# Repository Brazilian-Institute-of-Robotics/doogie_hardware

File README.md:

# Doogie Hardware
This repository is intend to gather all the files regarding the Doogie Mouse robot hardware and briefly explain about robot's electronic architecture.

## Folder organization
- [Eagle]\: [Autocad Eagle] files (*.sch and *.brd) of top and bottom boards and a file used to check design rules (.dru)
- [Gerbers]\: Files used to manufacture the top and bottom boards
- [Libraries]\: Eagle libraries used in the layout of the Doogie Mouse robot boards
- [Schematics]\: Electronic schematics of top and bottom board in PDF format
- [BOM]\: Bill Of Materials

## Electronic architecture
The electronic architecture in the figure below demonstrates how Doogie Mousee components are electrically interconnected. For the purpose of better visualization, the voltage reference (Ground - GND) was omitted.

<p align="center">
<b>Figure 1: </b>Electronic architecture 
<br>
<br>

</p>

The Doogie is equipped with a Li-Ion battery with 3.6 V of nominal voltage. To make the battery voltage level compatible with the other components, two DC-DC converters are used. The first will supply 6 V exclusively for motors and emitting LEDs. The second is responsible for supplying the Raspberry Pi with 5 V. However, the components that are connected to the Raspberry Pi are powered by 3.3 V through an internal DC-DC converter on the microprocessor system board.

In order to facilitate the replication of the robot by users who want to use it, it was decided to use breakout boards, which are pre-assembled electronic boards. Doogie has six of them: two DC-DC voltage converters, an A/D converter, an IMU, an analog multiplexer and an H-Bridge. The other components, such as resistors, transistors, infrared LEDs, phototransistors and connectors, are soldered directly on the PCB.

Doogie components communicate and are controlled in several ways. The A/D converter and the IMU communicate with the Raspberry Pi via an I2C bus. As the specified A/D converter has only 4 channels (one for each infrared sensor), it was decided to use an analog multiplexer to allow the battery voltage value to be obtained as well. This multiplexer is controlled by digital pins from the processing unit. Finally, the control of the motors is performed by an H bridge with two independent channels. This power driver allows the directions of rotation of the motors to be controlled by digital pins from the Raspberry Pi while the speed control is performed by PWM.

For detailed description of components connections, see the electronic schematics [doogie_bottom_board](Schematics/doogie_bottom_board.pdf) and [doogie_top_board](Schematics/doogie_top_board.pdf).

## Boards overview
<p align="center">
<b>Top Board</b>
<br>
<br>

</p>

<p align="center">
<b>Bottom Board</b>
<br>
<br>

</p>

## Assembly Instructions
See [Hardware Setup] on Doogie wiki page!

## Purpose of the Project

Doogie Mouse platform was originally developed in 2019 as an undergraduate thesis (Theoprax methodoly) at Centro Universitário SENAI CIMATEC in partnership with Brazillian Institute of Robotics, for teaching principles of artificial intelligence using high level framework for writing and reusing robot software.

It's a open source project and expects modifications and contributions from it's users. 

## Change Log
#### [1.0] - 2019-12-10
- First version

## Bugs & Feature Requests
Please report bugs and request features using the [Issue Tracker](https://github.com/Brazilian-Institute-of-Robotics/doogie_hardware/issues).

[Eagle]: https://github.com/Brazilian-Institute-of-Robotics/doogie_hardware/tree/master/Eagle
[Autocad Eagle]: https://www.autodesk.com/products/eagle/overview?geoNavigationPreferredSite=US
[Gerbers]: https://github.com/Brazilian-Institute-of-Robotics/doogie_hardware/tree/master/Gerbers
[Libraries]: https://github.com/Brazilian-Institute-of-Robotics/doogie_hardware/tree/master/Libraries
[Schematics]: https://github.com/Brazilian-Institute-of-Robotics/doogie_hardware/tree/master/Schematics
[BOM]: https://github.com/Brazilian-Institute-of-Robotics/doogie_hardware/tree/master/BOM
[Hardware Setup]: https://github.com/Brazilian-Institute-of-Robotics/doogie/wiki/Hardware-Setup

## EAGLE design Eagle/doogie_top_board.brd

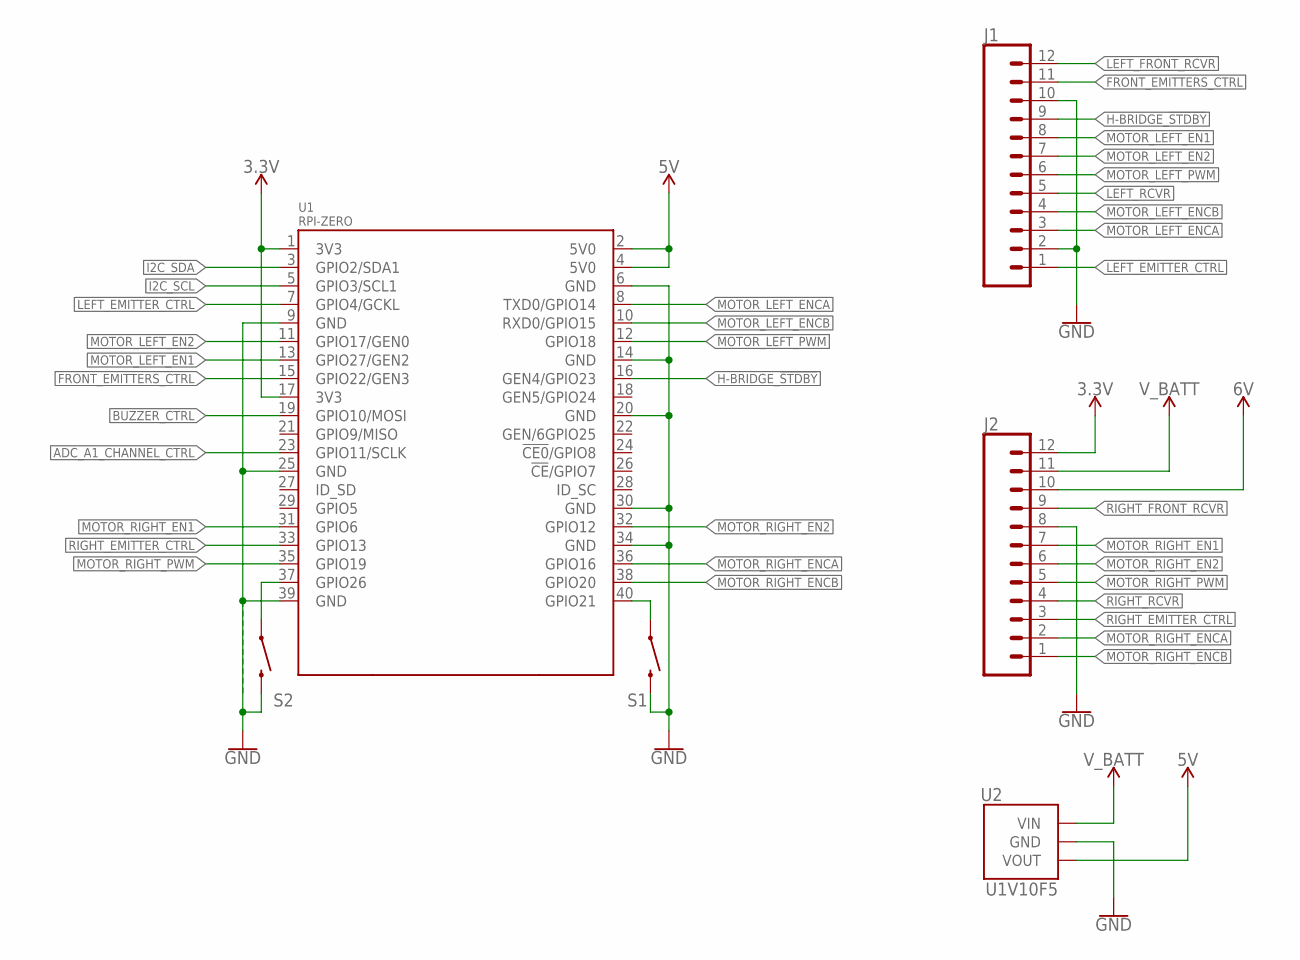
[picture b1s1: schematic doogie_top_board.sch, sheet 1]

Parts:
J1, J2: CONN_12; 1X12
S1, S2: MOMENTARY-SWITCH-SPST-PTH-6.0MM; TACTILE_SWITCH_PTH_6.0MM
U1: RPI-ZERO; RASPBERRYPI_BASTELSTUBE_V13_RASPI_BOARD_B+_FULL
U2: U1V10F5

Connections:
3.3V: J2.12, U1.1 (3V3), U1.17 (3V3); also elsewhere on the board
5V: U1.2 (5V0), U1.4 (5V0), U2.VOUT; also elsewhere on the board
ADC_A1_CHANNEL_CTRL: U1.23 (GPIO11/SCLK); also elsewhere on the board
BUZZER_CTRL: U1.19 (GPIO10/MOSI); also elsewhere on the board
FRONT_EMITTERS_CTRL: J1.11, U1.15 (GPIO22/GEN3)
GND: J1.2, J1.10, J2.8, S1.3 (2), S2.3 (2), U1.6 (GND), U1.9 (GND), U1.14 (GND), U1.20 (GND), U1.25 (GND), U1.30 (GND), U1.34 (GND), U1.39 (GND), U2.GND; also elsewhere on the board
H-BRIDGE_!STDBY: J1.9, U1.16 (GEN4/GPIO23)
I2C_SCL: U1.5 (GPIO3/SCL1); also elsewhere on the board
I2C_SDA: U1.3 (GPIO2/SDA1); also elsewhere on the board
LEFT_EMITTER_CTRL: J1.1, U1.7 (GPIO4/GCKL)
LEFT_FRONT_RCVR: J1.12; also elsewhere on the board
LEFT_RCVR: J1.5; also elsewhere on the board
MOTOR_LEFT_EN1: J1.8, U1.13 (GPIO27/GEN2)
MOTOR_LEFT_EN2: J1.7, U1.11 (GPIO17/GEN0)
MOTOR_LEFT_ENCA: J1.3, U1.8 (TXD0/GPIO14)
MOTOR_LEFT_ENCB: J1.4, U1.10 (RXD0/GPIO15)
MOTOR_LEFT_PWM: J1.6, U1.12 (GPIO18)
MOTOR_RIGHT_EN1: J2.7, U1.31 (GPIO6)
MOTOR_RIGHT_EN2: J2.6, U1.32 (GPIO12)
MOTOR_RIGHT_ENCA: J2.2, U1.36 (GPIO16)
MOTOR_RIGHT_ENCB: J2.1, U1.38 (GPIO20)
MOTOR_RIGHT_PWM: J2.5, U1.35 (GPIO19)
unnamed: S2.1, U1.37 (GPIO26)
unnamed: S1.1, U1.40 (GPIO21)
RIGHT_EMITTER_CTRL: J2.3, U1.33 (GPIO13)
RIGHT_FRONT_RCVR: J2.9; also elsewhere on the board
RIGHT_RCVR: J2.4; also elsewhere on the board
VOUT: J2.10; also elsewhere on the board
V_BATT: J2.11, U2.VIN; also elsewhere on the board

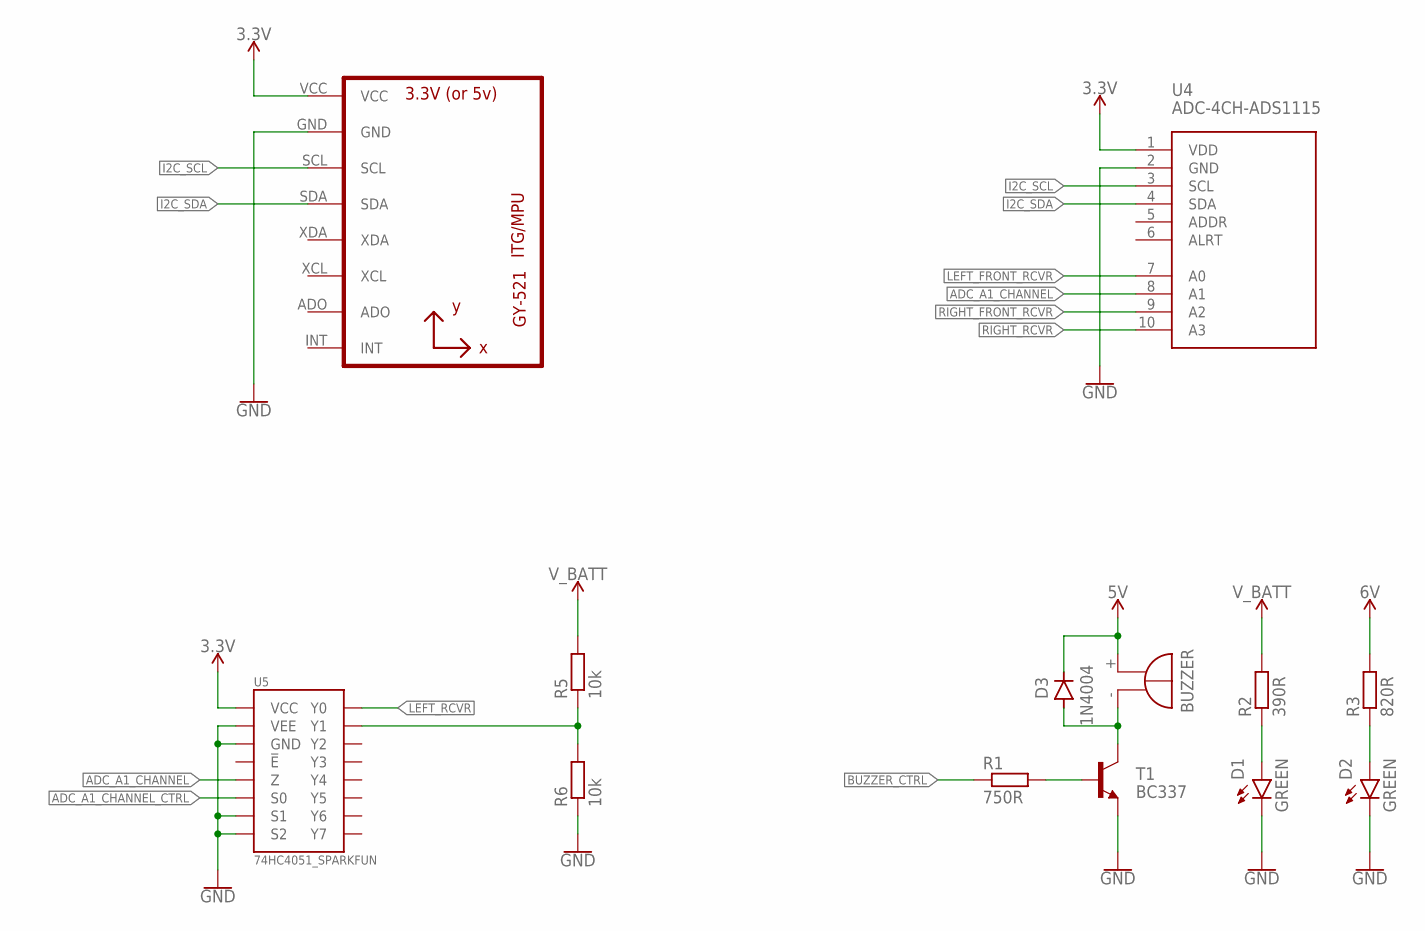
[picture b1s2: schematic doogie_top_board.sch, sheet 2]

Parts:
BUZZER: F/TMB
D1, D2: GREEN; LED_3MM
D3: 1N4004; DO41-10
R1: 750R; 0204/7
R2: 390R; 0204/7
R3: 820R; 0204/7
R5, R6: 10k; 0204/7
T1: BC337; TO92
U3: GY-521MPU6050; GY-521
U4: ADC-4CH-ADS1115
U5: 74HC4051_SPARKFUN

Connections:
3.3V: U3.VCC, U4.1 (VDD), U5.VCC, U5.VCC@1 (VCC); also elsewhere on the board
5V: BUZZER.+, D3.C; also elsewhere on the board
ADC_A1_CHANNEL: U4.8 (A1), U5.Z
ADC_A1_CHANNEL_CTRL: U5.S0; also elsewhere on the board
BUZZER_CTRL: R1.1; also elsewhere on the board
GND: D1.K (C), D2.K (C), R6.1, T1.1 (E), U3.GND, U4.2 (GND), U5.GND, U5.GND@1 (GND), U5.S1, U5.S2, U5.VEE, U5.VEE@1 (VEE); also elsewhere on the board
I2C_SCL: U3.SCL, U4.3 (SCL); also elsewhere on the board
I2C_SDA: U3.SDA, U4.4 (SDA); also elsewhere on the board
LEFT_FRONT_RCVR: U4.7 (A0); also elsewhere on the board
LEFT_RCVR: U5.Y0; also elsewhere on the board
unnamed: BUZZER.-, D3.A, T1.3 (C)
unnamed: R1.2, T1.2 (B)
unnamed: D1.A, R2.1
unnamed: D2.A, R3.1
unnamed: R5.1, R6.2, U5.Y1
RIGHT_FRONT_RCVR: U4.9 (A2); also elsewhere on the board
RIGHT_RCVR: U4.10 (A3); also elsewhere on the board
VOUT: R3.2; also elsewhere on the board
V_BATT: R2.2, R5.2; also elsewhere on the board

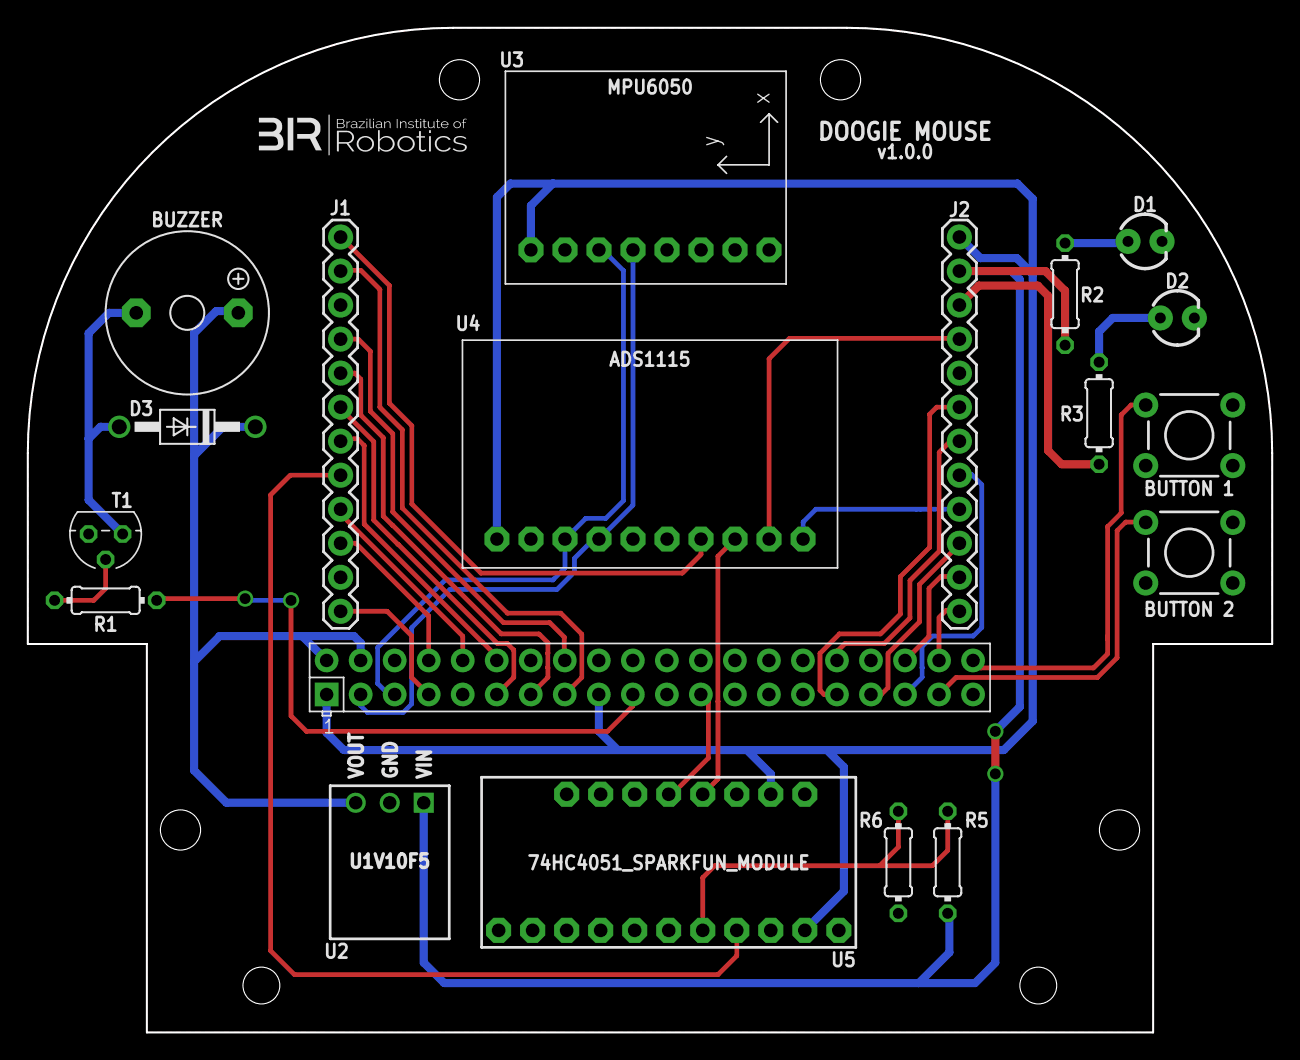
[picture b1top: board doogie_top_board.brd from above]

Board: 2 copper layers, 92.9 x 75.0 mm, 19 parts (0 on the bottom side), 35 nets.

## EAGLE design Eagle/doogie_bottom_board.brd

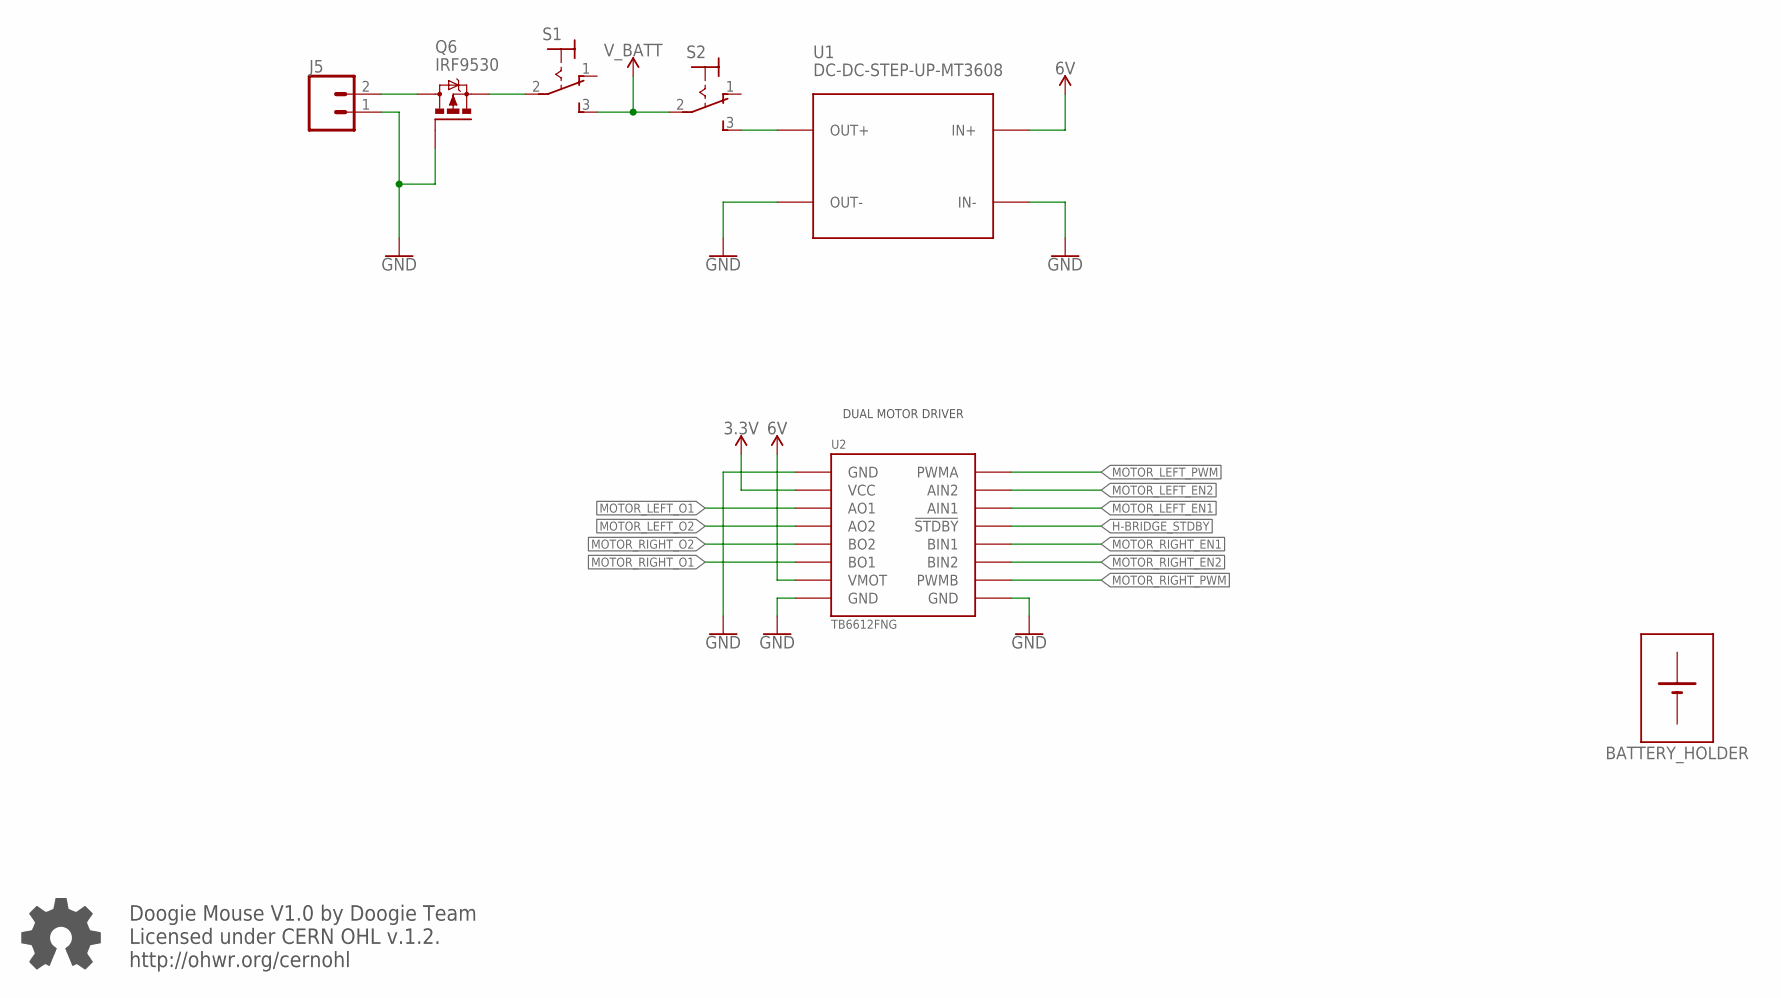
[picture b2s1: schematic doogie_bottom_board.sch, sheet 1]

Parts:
BATTERY_HOLDER: BATTERY_HOLDER
J5: CONN_02JST-PTH-2; JST-2-PTH
Q6: IRF9530; TO220BV
S1, S2: M9040P
U1: DC-DC-STEP-UP-MT3608
U2: TB6612FNG

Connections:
3.3V: U2.2 (VCC); also elsewhere on the board
6V: U1.IN+, U2.7 (VMOT); also elsewhere on the board
FILLING_POLYGON: J5.1, Q6.G, U1.IN-, U1.OUT-, U2.1 (GND), U2.8 (GND), U2.16 (GND); also elsewhere on the board
H-BRIDGE_!STDBY: U2.12 (!STDBY!); also elsewhere on the board
MOTOR_LEFT_EN1: U2.11 (AIN1); also elsewhere on the board
MOTOR_LEFT_EN2: U2.10 (AIN2); also elsewhere on the board
MOTOR_LEFT_O1: U2.3 (AO1); also elsewhere on the board
MOTOR_LEFT_O2: U2.4 (AO2); also elsewhere on the board
MOTOR_LEFT_PWM: U2.9 (PWMA); also elsewhere on the board
MOTOR_RIGHT_EN1: U2.13 (BIN1); also elsewhere on the board
MOTOR_RIGHT_EN2: U2.14 (BIN2); also elsewhere on the board
MOTOR_RIGHT_O1: U2.6 (BO1); also elsewhere on the board
MOTOR_RIGHT_O2: U2.5 (BO2); also elsewhere on the board
MOTOR_RIGHT_PWM: U2.15 (PWMB); also elsewhere on the board
unnamed: S2.3 (S), U1.OUT+
unnamed: J5.2, Q6.D
unnamed: Q6.S, S1.2
V_BATT: S1.3 (S), S2.2; also elsewhere on the board

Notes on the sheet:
Doogie Mouse V1.0 by Doogie Team Licensed under CERN OHL v.1.2. http://ohwr.org/cernohl
DUAL MOTOR DRIVER

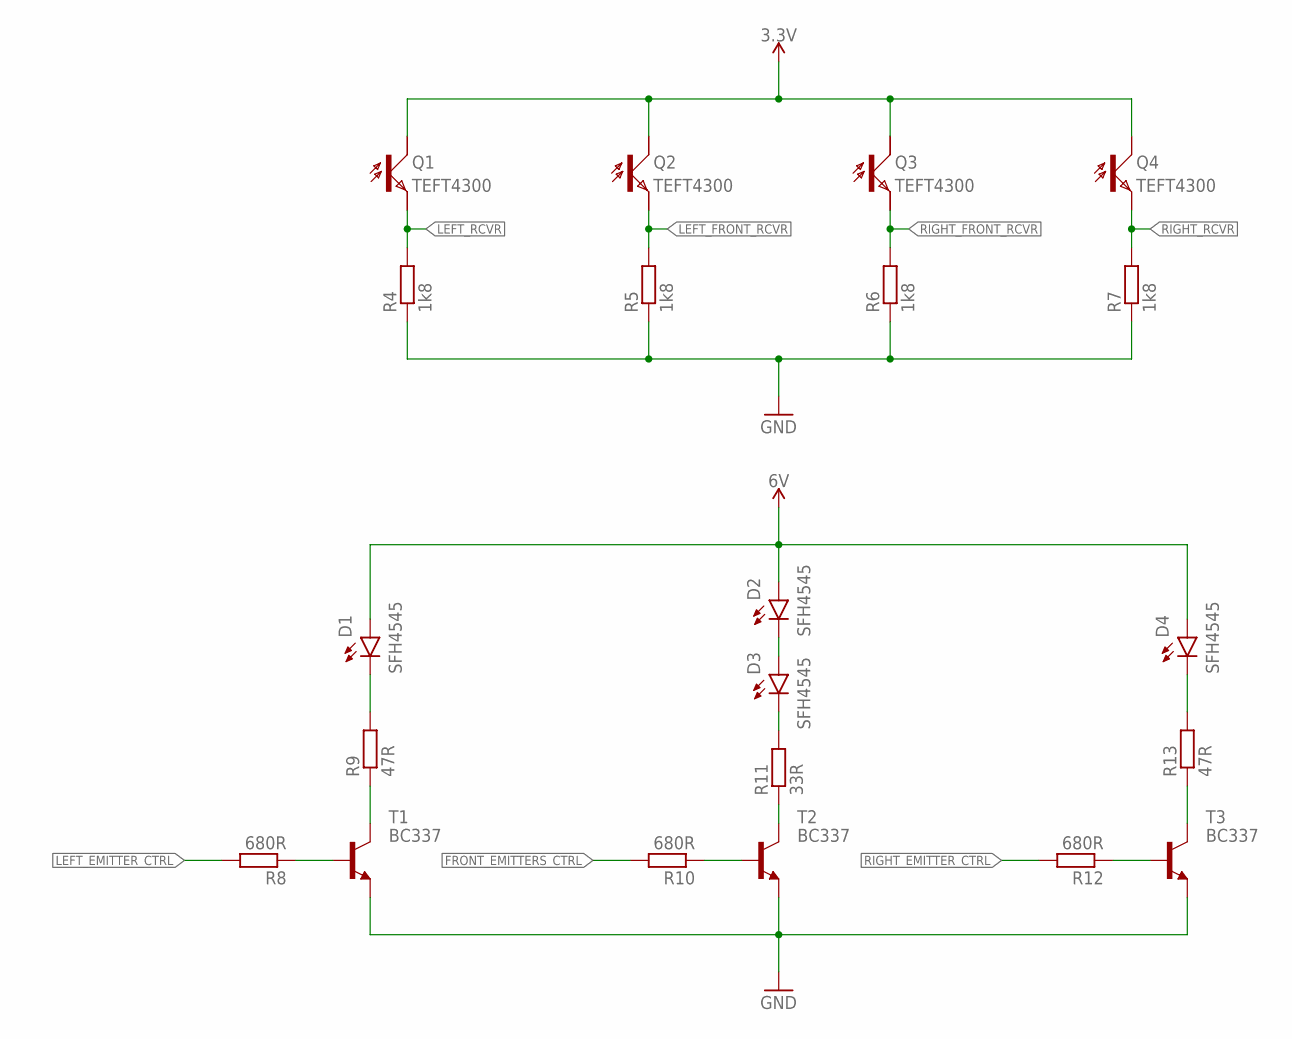
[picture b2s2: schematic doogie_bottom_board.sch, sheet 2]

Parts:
D1, D2, D3, D4: SFH4545; SFH4545-AK
Q1, Q2, Q3, Q4: TEFT4300; TEFT_5MM_RA
R4, R5, R6, R7: 1k8; 0204/7
R8, R10, R12: 680R; 0204/7
R9, R13: 47R; 0204/7
R11: 33R; 0204/7
T1, T2, T3: BC337; TO92

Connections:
3.3V: Q1.C, Q2.C, Q3.C, Q4.C; also elsewhere on the board
6V: D1.A, D2.A, D4.A; also elsewhere on the board
FILLING_POLYGON: R4.1, R5.1, R6.1, R7.1, T1.1 (E), T2.1 (E), T3.1 (E); also elsewhere on the board
FRONT_EMITTERS_CTRL: R10.2; also elsewhere on the board
LEFT_EMITTER_CTRL: R8.2; also elsewhere on the board
LEFT_FRONT_RCVR: Q2.E, R5.2; also elsewhere on the board
LEFT_RCVR: Q1.E, R4.2; also elsewhere on the board
unnamed: R9.1, T1.3 (C)
unnamed: R11.1, T2.3 (C)
unnamed: R13.1, T3.3 (C)
unnamed: R8.1, T1.2 (B)
unnamed: R10.1, T2.2 (B)
unnamed: R12.1, T3.2 (B)
unnamed: D2.K (C), D3.A
unnamed: D1.K (C), R9.2
unnamed: D4.K (C), R13.2
unnamed: D3.K (C), R11.2
RIGHT_EMITTER_CTRL: R12.2; also elsewhere on the board
RIGHT_FRONT_RCVR: Q3.E, R6.2; also elsewhere on the board
RIGHT_RCVR: Q4.E, R7.2; also elsewhere on the board

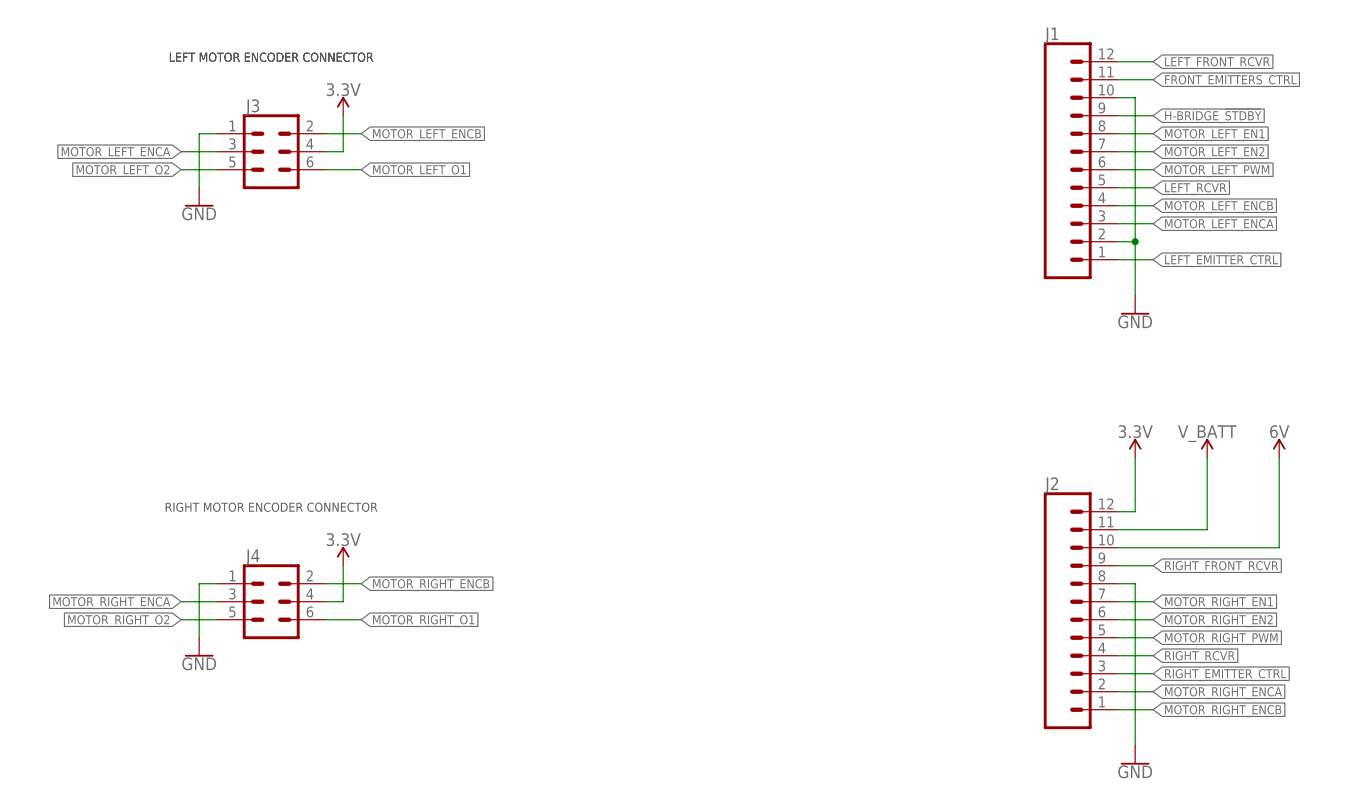
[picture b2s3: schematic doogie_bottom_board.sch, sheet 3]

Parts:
J1, J2: CONN_12; 1X12
J3, J4: CONN_03X2SHROUD; 2X3-SHROUDED

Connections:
3.3V: J2.12, J3.4, J4.4; also elsewhere on the board
6V: J2.10; also elsewhere on the board
FILLING_POLYGON: J1.2, J1.10, J2.8, J3.1, J4.1; also elsewhere on the board
FRONT_EMITTERS_CTRL: J1.11; also elsewhere on the board
H-BRIDGE_!STDBY: J1.9; also elsewhere on the board
LEFT_EMITTER_CTRL: J1.1; also elsewhere on the board
LEFT_FRONT_RCVR: J1.12; also elsewhere on the board
LEFT_RCVR: J1.5; also elsewhere on the board
MOTOR_LEFT_EN1: J1.8; also elsewhere on the board
MOTOR_LEFT_EN2: J1.7; also elsewhere on the board
MOTOR_LEFT_ENCA: J1.3, J3.3
MOTOR_LEFT_ENCB: J1.4, J3.2
MOTOR_LEFT_O1: J3.6; also elsewhere on the board
MOTOR_LEFT_O2: J3.5; also elsewhere on the board
MOTOR_LEFT_PWM: J1.6; also elsewhere on the board
MOTOR_RIGHT_EN1: J2.7; also elsewhere on the board
MOTOR_RIGHT_EN2: J2.6; also elsewhere on the board
MOTOR_RIGHT_ENCA: J2.2, J4.3
MOTOR_RIGHT_ENCB: J2.1, J4.2
MOTOR_RIGHT_O1: J4.6; also elsewhere on the board
MOTOR_RIGHT_O2: J4.5; also elsewhere on the board
MOTOR_RIGHT_PWM: J2.5; also elsewhere on the board
RIGHT_EMITTER_CTRL: J2.3; also elsewhere on the board
RIGHT_FRONT_RCVR: J2.9; also elsewhere on the board
RIGHT_RCVR: J2.4; also elsewhere on the board
V_BATT: J2.11; also elsewhere on the board

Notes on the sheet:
LEFT MOTOR ENCODER CONNECTOR
RIGHT MOTOR ENCODER CONNECTOR

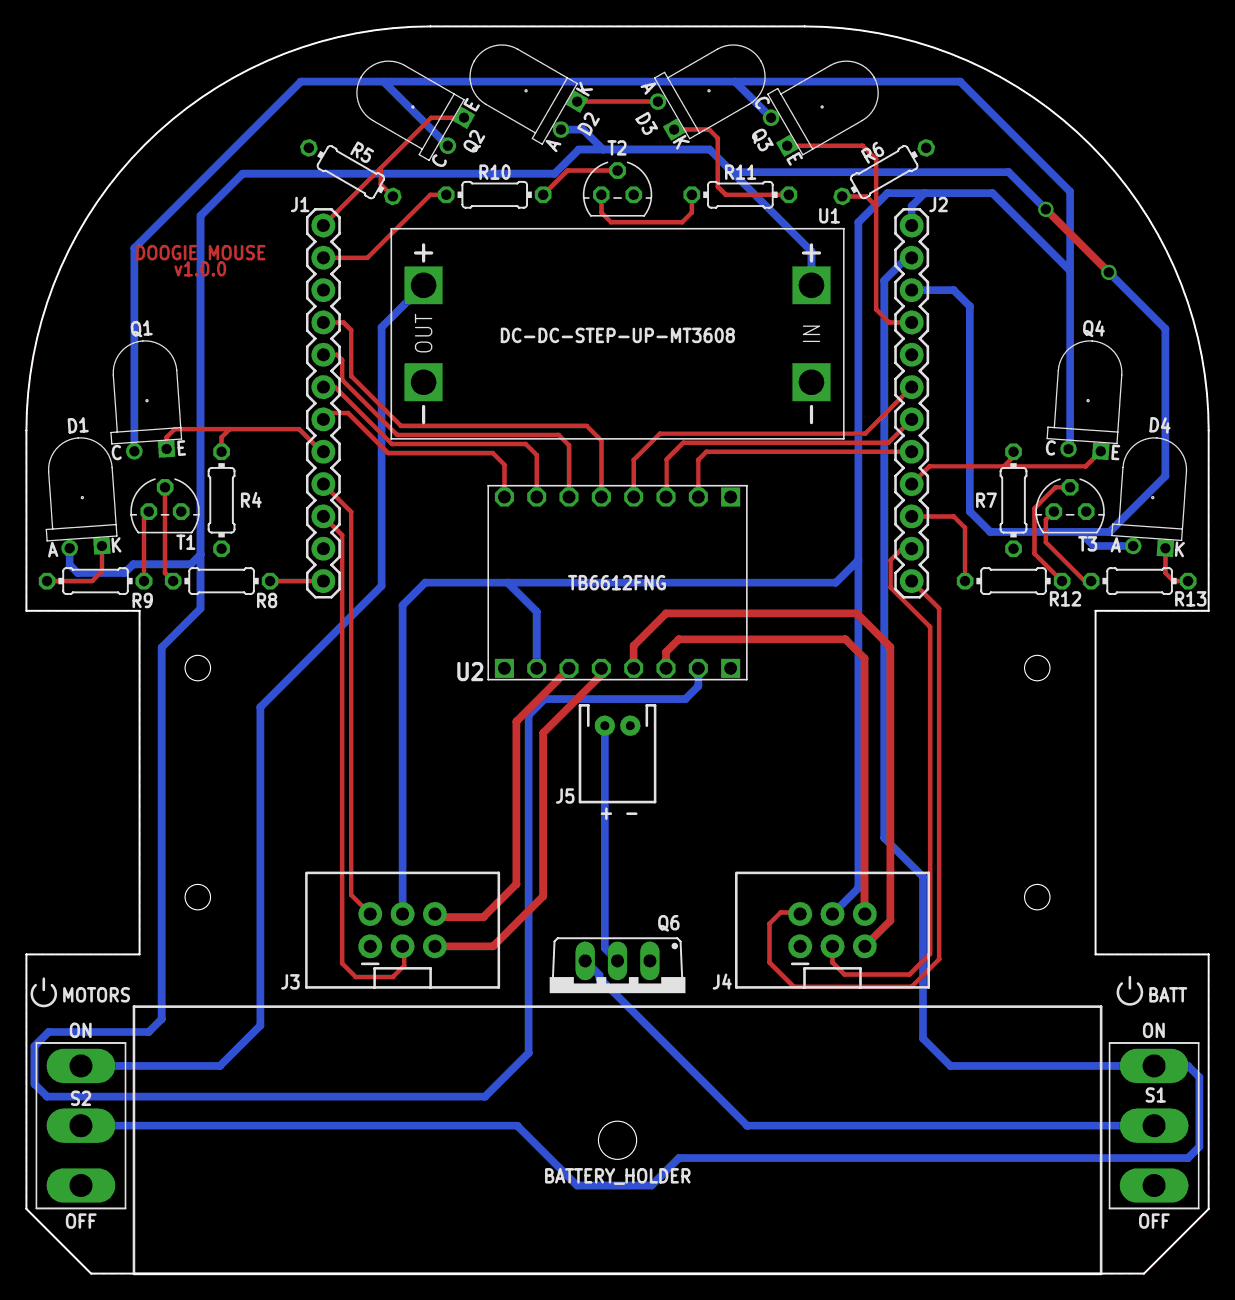
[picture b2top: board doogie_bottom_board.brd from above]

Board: 2 copper layers, 92.9 x 98.0 mm, 32 parts (0 on the bottom side), 39 nets.

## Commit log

2019-06-28 Add pdf files
2019-07-04 Remove unnecessary stuffs
2019-07-17 Add top board
2019-07-28 Add first version of schematics
2019-07-29 Add first version of thebottom board routed
2019-07-29 Change net order and names
2019-07-29 Remove the now ignored directory Eagle_Libraries
2019-08-17 Route bottom board
2019-08-20 Make top board routing sketch
2019-08-22 Add first step of top board routing
2019-08-24 Add silk
2019-08-26 Change robot name on silk
2019-08-26 Add H-bridge name on bottom board silk
2019-08-26 Add DC-DC name on silk
2019-08-26 Add extra holes on top board
2019-08-26 Fiz backanotation error
2019-10-01 Fix copper traces of I2C bus
2019-10-01 Add Gerbers and Schematics files
2019-10-01 Change colors on manufacturing visualization
2019-10-04 Add design check rules file
2019-10-04 Add libraries used in the Eagle project
2019-10-07 Add BIR logo in page frame
2019-10-07 Add dril gerbers files
2019-10-07 Update schematics
2020-03-21 Add electronics explanation in README
2020-03-21 Add Bill Of Materials
2020-03-22 Add topics in README

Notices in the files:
parts and their libraries:
diy-modules: Released under the Creative Commons Attribution 4.0 International License: http://creativecommons.org/licenses/by/4.0
SparkFun-Connectors: Licensing: Creative Commons ShareAlike 4.0 International - https://creativecommons.org/licenses/by-sa/4.0
